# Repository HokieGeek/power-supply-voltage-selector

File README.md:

# power-supply-voltage-selector 
Trying to learn more electronics by building a circuit that lets me have different voltage outputs for use with other prototypes and mostly breadboards

## Prototype

# Schematics
## Primary

## Daughter

# Boards
## Primary

## Daughter

# Parts list
## ICs
* [ATTINY85](http://www.atmel.com/images/atmel-2586-avr-8-bit-microcontroller-attiny25-attiny45-attiny85_datasheet.pdf) - Drives the digi pot and shift register
* [LM7805CT](http://www.mouser.com/ds/2/149/LM7805-189995.pdf) - 5v voltage regulator for Vic
* [MIC2940](http://www.micrel.com/_PDF/mic2940.pdf) - Adjustable voltage regulator as target output regulator
* [MCP41010](http://ww1.microchip.com/downloads/en/DeviceDoc/11195c.pdf) - 10 kΩ digital potentiometer
* [SN74LS595N](http://www.ti.com/lit/ds/symlink/sn74ls596.pdf) - 8-bit shift registers with latches

## Discrete components
* 12V Transformer
* 4x 1N4007 Rectifiers
* 2x 47 µF Electrolytic capacitors
* 3x 0.1 µF Ceramic capacitors
* 1x 330 Ω Resistor network (SIL-6)
* 1x 10 kΩ 5% Resistors
* 2x 1 kΩ 5% Resistors
* 4x 3mm LEDs (green. To indicate selected voltage)
* 1x 3mm LED (red. To indicate that power is flowing from the wall)
* 1x USB-A Female
* LED Volt meter thingy (slightly redundant with the LEDs...)
* Toggle switch (turns on Vin)
* Momentatry switch (selects voltage)
* Jumpers and headers (Oh my!)

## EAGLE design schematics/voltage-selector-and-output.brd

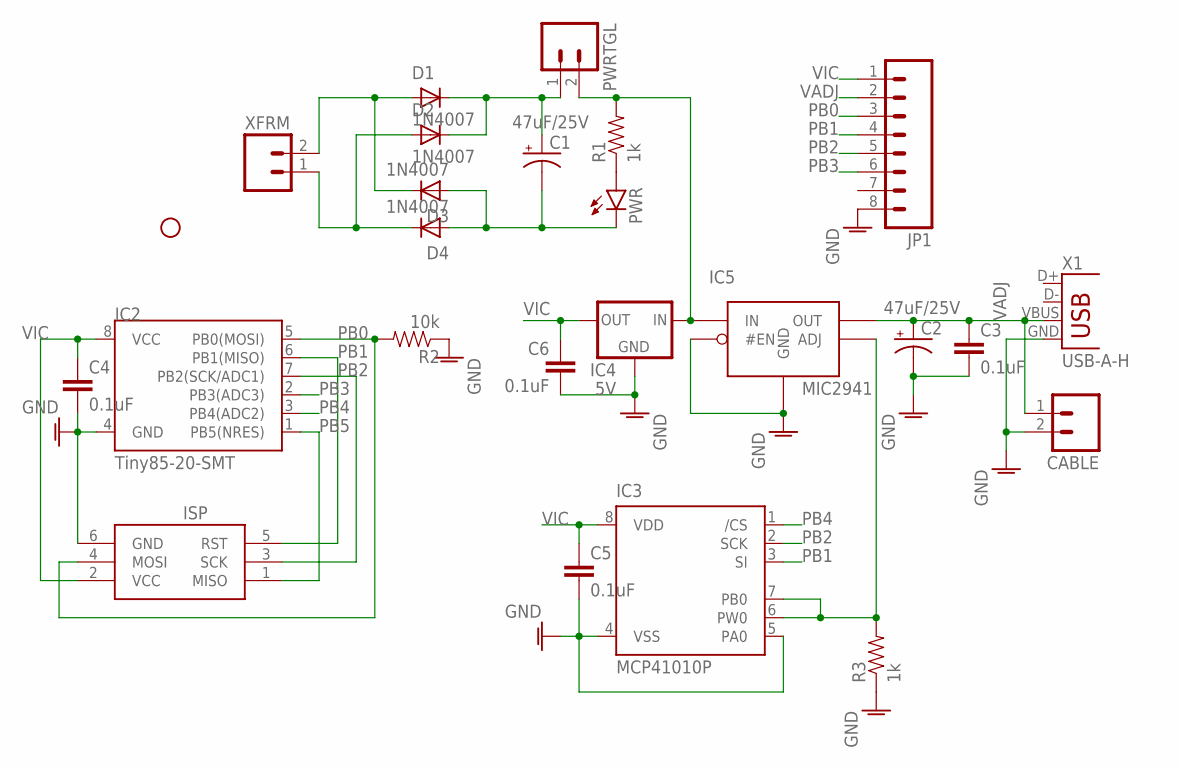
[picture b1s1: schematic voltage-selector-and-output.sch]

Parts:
C1, C2: 47uF/25V; E2,5-6
C3, C4, C5, C6: 0.1uF; 0805-CAP
CABLE: M02PTH; 1X02
D1, D2, D3, D4: 1N4007; SMA-DO214AC
IC2: Tiny85-20-SMT; SO08-EIAJ
IC3: MCP41010P; DIL8
IC4: 5V; 78XXS
IC5: MIC2941; TO220-5
ISP: AVRISP-6; AVRISP
JP1: M081X08; 1X08
PWR: LED-3MM-NO_SILK; LED3MM-NS
PWRTGL: M02PTH; 1X02
R1, R3: 1k; 0805
R2: 10k; 0805
STANDOFF1: STAND-OFF
X1: USB-A-H
XFRM: M02PTH; 1X02

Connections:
AGND: C2.-, C3.2, C4.2, C5.2, C6.2, CABLE.2, IC2.4 (GND), IC3.4 (VSS), IC3.5 (PA0), IC4.GND, IC5.2 (#EN), IC5.3 (GND), ISP.6 (GND), JP1.8, R2.1, R3.1, X1.GND
GND: D2.A, D4.K (C), XFRM.1
unnamed: IC3.6 (PW0), IC3.7 (PB0), IC5.1 (ADJ), R3.2
unnamed: D1.A, D3.K (C), XFRM.2
unnamed: PWR.A, R1.1
unnamed: C1.-, D3.A, D4.A, PWR.K (C)
unnamed: C1.+, D1.K (C), D2.K (C), PWRTGL.1
PB0: IC2.5 (PB0(MOSI)), ISP.4 (MOSI), JP1.3, R2.2
PB1: IC2.6 (PB1(MISO)), IC3.3 (SI), ISP.5 (RST), JP1.4
PB2: IC2.7 (PB2(SCK/ADC1)), IC3.2 (SCK), ISP.3 (SCK), JP1.5
PB3: IC2.2 (PB3(ADC3)), JP1.6
PB4: IC2.3 (PB4(ADC2)), IC3.1 (/CS)
PB5: IC2.1 (PB5(NRES)), ISP.1 (MISO)
VADJ: C2.+, C3.1, CABLE.1, IC5.5 (OUT), JP1.2, X1.VBUS
VCC: IC4.IN, IC5.4 (IN), PWRTGL.2, R1.2
VIC: C4.1, C5.1, C6.1, IC2.8 (VCC), IC3.8 (VDD), IC4.OUT, ISP.2 (VCC), JP1.1

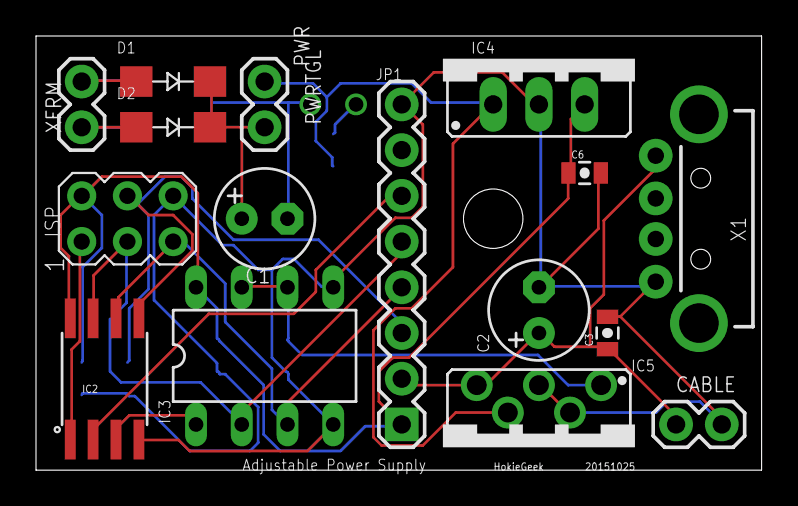
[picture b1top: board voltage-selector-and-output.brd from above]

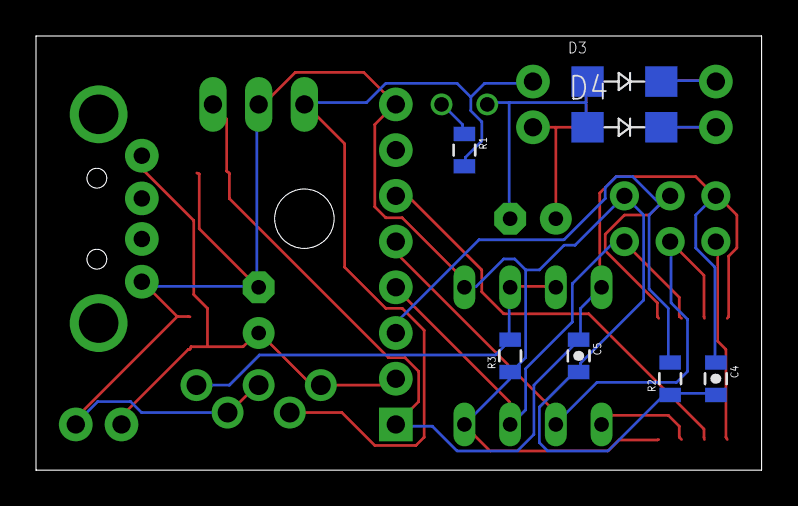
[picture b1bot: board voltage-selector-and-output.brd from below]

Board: 2 copper layers, 40.3 x 24.1 mm, 25 parts (7 on the bottom side), 16 nets.

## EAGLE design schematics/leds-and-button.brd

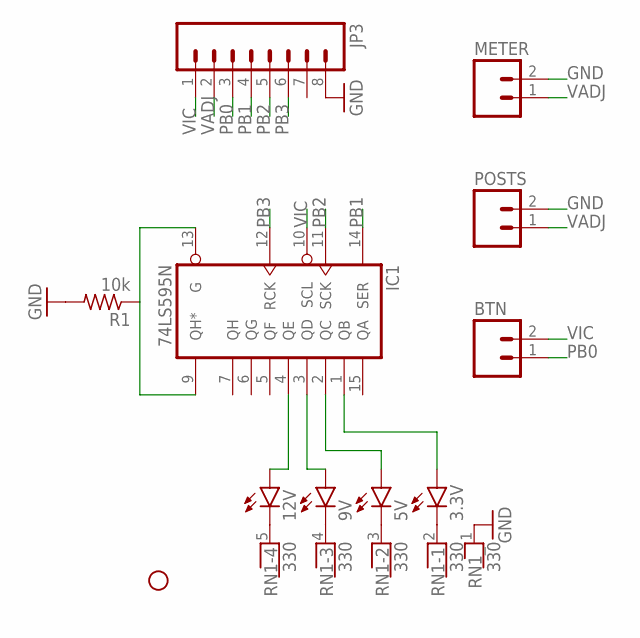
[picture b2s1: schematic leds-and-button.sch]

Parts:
3.3V, 5V, 9V, 12V: LED3MM
BTN: M02PTH; 1X02
IC1: 74LS595N; DIL16
JP2: STAND-OFF
JP3: M081X08; 1X08
METER: M02PTH; 1X02
POSTS: M02PTH; 1X02
R1: 10k; 0204V
RN1: 330; RN-6

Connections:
GND: IC1.8 (GND), JP3.8, METER.2, POSTS.2, R1.2, RN1.1
unnamed: 12V.K (C), RN1.5
unnamed: 9V.K (C), RN1.4
unnamed: 12V.A, IC1.4 (QE)
unnamed: 9V.A, IC1.3 (QD)
unnamed: 5V.A, IC1.2 (QC)
unnamed: 5V.K (C), RN1.3
unnamed: 3.3V.K (C), RN1.2
unnamed: IC1.9 (QH*), IC1.13 (G), R1.1
unnamed: 3.3V.A, IC1.1 (QB)
PB0: BTN.1, JP3.3
PB1: IC1.14 (SER), JP3.4
PB2: IC1.11 (SCK), JP3.5
PB3: IC1.12 (RCK), JP3.6
VADJ: IC1.16 (VCC), JP3.2, METER.1, POSTS.1
VIC: BTN.2, IC1.10 (SCL), JP3.1

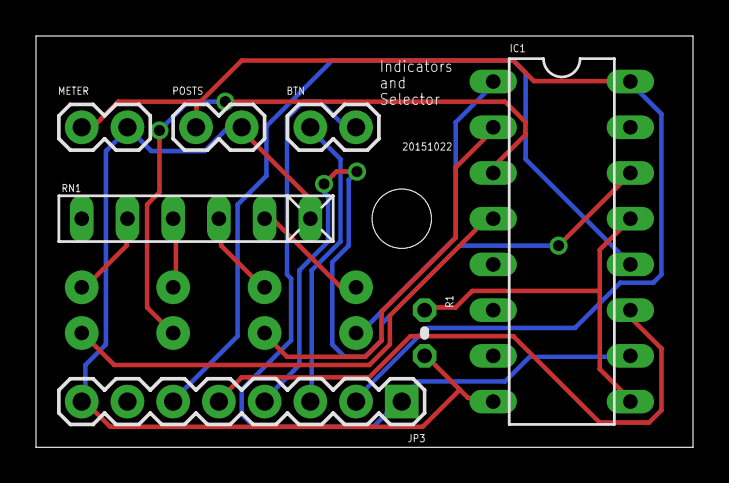
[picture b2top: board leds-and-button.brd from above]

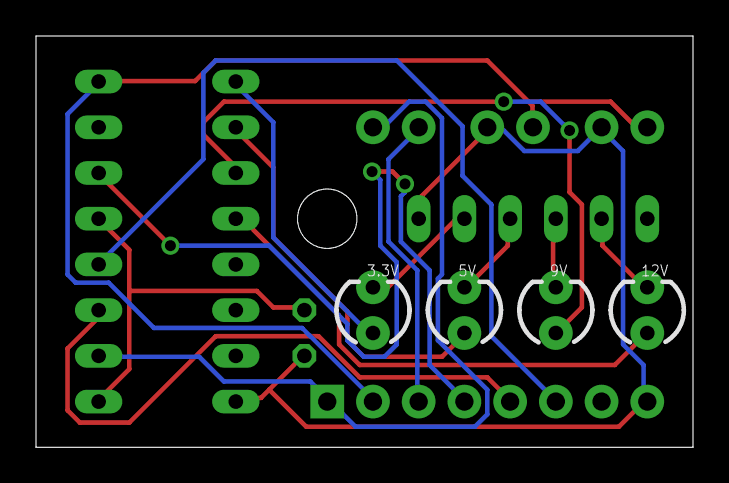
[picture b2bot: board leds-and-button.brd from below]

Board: 2 copper layers, 36.5 x 22.9 mm, 12 parts (4 on the bottom side), 16 nets.

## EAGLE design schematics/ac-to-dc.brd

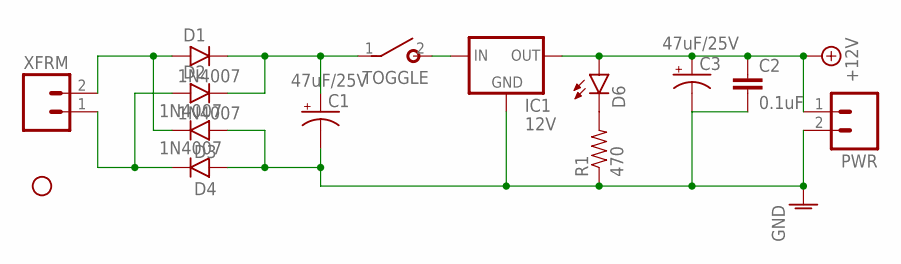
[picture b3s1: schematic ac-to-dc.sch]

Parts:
C1, C3: 47uF/25V; E2,5-6
C2: 0.1uF; CAP-PTH-SMALL
D1, D2, D3, D4: 1N4007; DO41-3
D6: LED-3MM-NO_SILK; LED3MM-NS
IC1: 12V; 78XXS
JP1: STAND-OFF
PWR: M02PTH; 1X02
R1: 470; AXIAL-0.4
TOGGLE: SPST
XFRM: M02PTH; 1X02

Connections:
+12V: C2.1, C3.+, D6.A, IC1.OUT, PWR.1
AGND: C1.-, C2.2, C3.-, D3.A, D4.A, IC1.GND, PWR.2, R1.P$1 (1)
unnamed: IC1.IN, TOGGLE.2 (S)
unnamed: D1.A, D3.C, XFRM.2
unnamed: D2.A, D4.C, XFRM.1
unnamed: D6.K (C), R1.P$2 (2)
unnamed: C1.+, D1.C, D2.C, TOGGLE.1

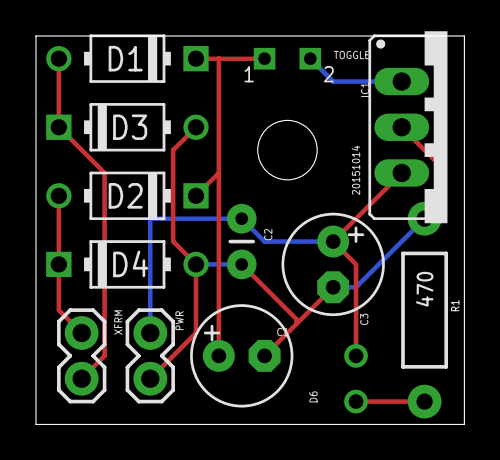
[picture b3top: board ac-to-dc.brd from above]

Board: 2 copper layers, 23.8 x 21.6 mm, 14 parts (0 on the bottom side), 7 nets.

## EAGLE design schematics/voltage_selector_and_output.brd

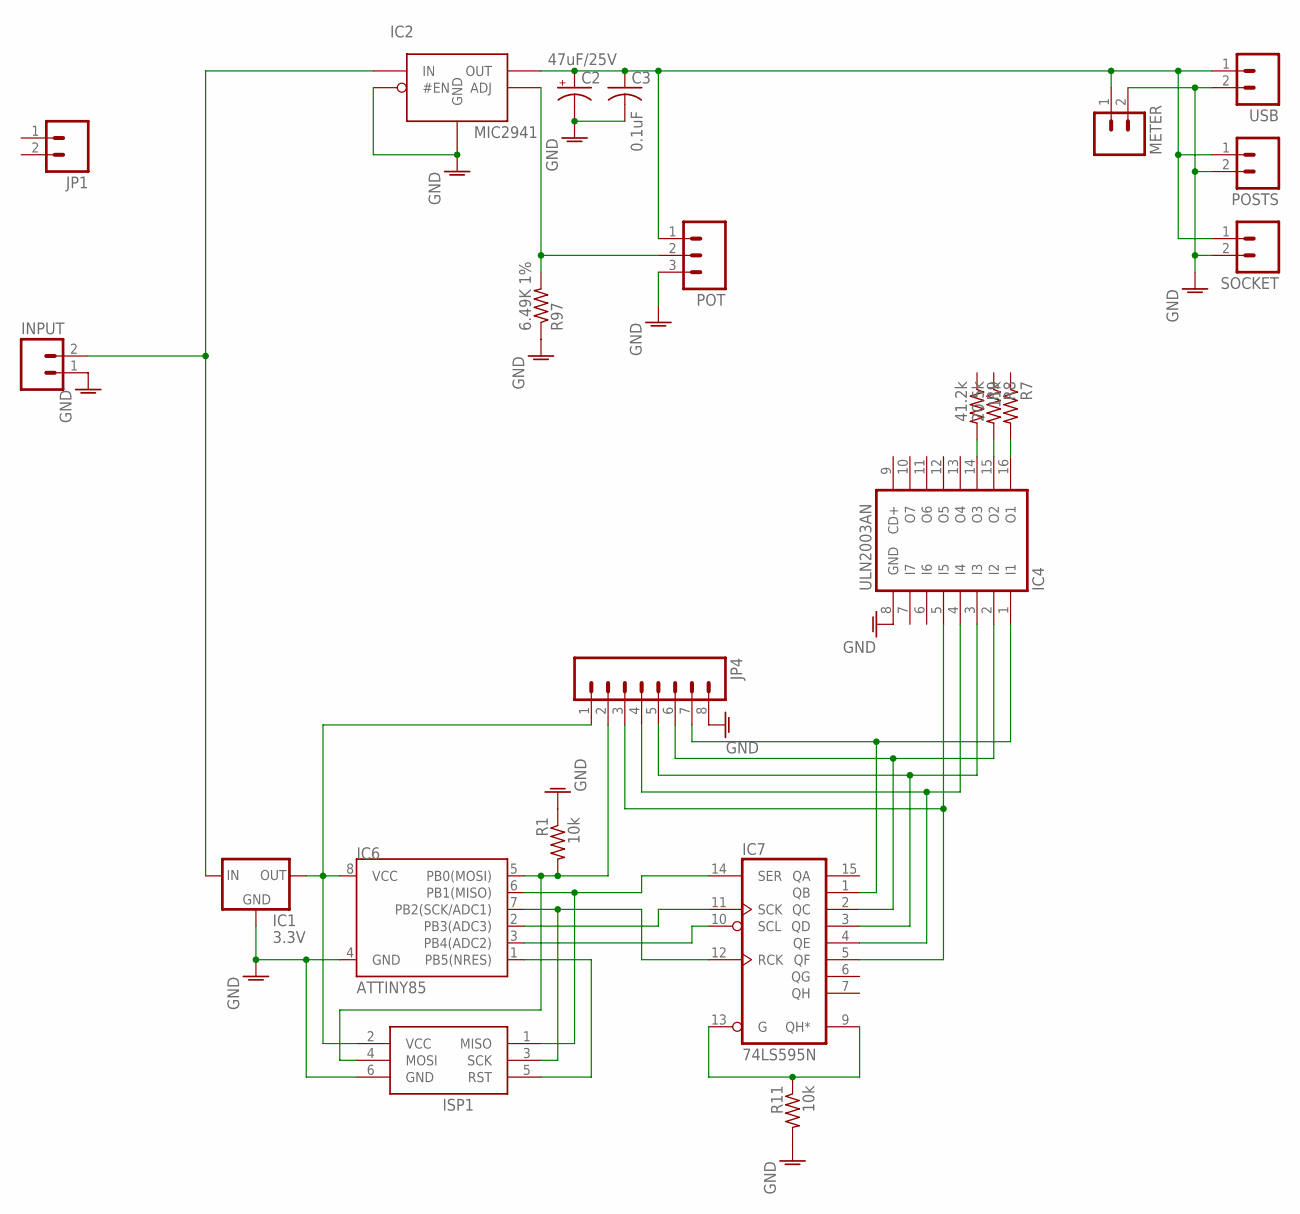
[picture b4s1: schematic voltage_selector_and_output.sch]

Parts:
C2: 47uF/25V; E2,5-6
C3: 0.1uF; C025-025X050
IC1: 3.3V; 78XXS
IC2: MIC2941; TO220-5
IC4: ULN2003AN; DIL16
IC6: ATTINY85; DIP08
IC7: 74LS595N; DIL16
INPUT: M02PTH; 1X02
ISP1: AVRISP-6; AVRISP
JP1: M02JST-PTH-2; JST-2-PTH
JP4: M081X08; 1X08
METER: M02PTH; 1X02
POSTS: M02PTH; 1X02
POT: M03PTH; 1X03
R1, R11: 10k; 0207/5V
R7: 11k; 0207/5V
R8: 20.5k; 0207/5V
R9: 41.2k; 0207/5V
R97: 6.49K 1%; 0207/5V
SOCKET: M02PTH; 1X02
USB: M02PTH; 1X02

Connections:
AGND: C2.-, C3.2, IC1.GND, IC2.2 (#EN), IC2.3 (GND), IC4.8 (GND), IC6.4 (GND), INPUT.1, ISP1.6 (GND), JP4.8, METER.2, POSTS.2, POT.3, R1.1, R11.2, R97.1, SOCKET.2, USB.2
GND: IC7.8 (GND)
ISP_VCC: IC1.OUT, IC6.8 (VCC), ISP1.2 (VCC), JP4.1
unnamed: IC1.IN, IC2.4 (IN), INPUT.2
unnamed: IC2.1 (ADJ), POT.2, R97.2
unnamed: IC6.1 (PB5(NRES)), ISP1.5 (RST)
unnamed: IC6.2 (PB3(ADC3)), IC7.11 (SCK)
unnamed: IC6.3 (PB4(ADC2)), IC7.10 (SCL)
unnamed: IC6.7 (PB2(SCK/ADC1)), IC7.12 (RCK), ISP1.3 (SCK)
unnamed: IC6.5 (PB0(MOSI)), ISP1.4 (MOSI), JP4.2, R1.2
unnamed: IC4.16 (O1), R7.2
unnamed: IC6.6 (PB1(MISO)), IC7.14 (SER), ISP1.1 (MISO)
unnamed: IC4.15 (O2), R8.2
unnamed: IC4.14 (O3), R9.2
unnamed: IC4.1 (I1), IC7.1 (QB), JP4.7
unnamed: IC4.2 (I2), IC7.2 (QC), JP4.6
unnamed: IC4.3 (I3), IC7.3 (QD), JP4.5
unnamed: IC4.4 (I4), IC7.4 (QE), JP4.4
unnamed: IC4.5 (I5), IC7.5 (QF), JP4.3
unnamed: IC7.9 (QH*), IC7.13 (G), R11.1
VADJ: C2.+, C3.1, IC2.5 (OUT), METER.1, POSTS.1, POT.1, SOCKET.1, USB.1
VCC: IC7.16 (VCC)

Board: 2 copper layers, 22 parts (0 on the bottom side), 20 nets, no tracks yet.

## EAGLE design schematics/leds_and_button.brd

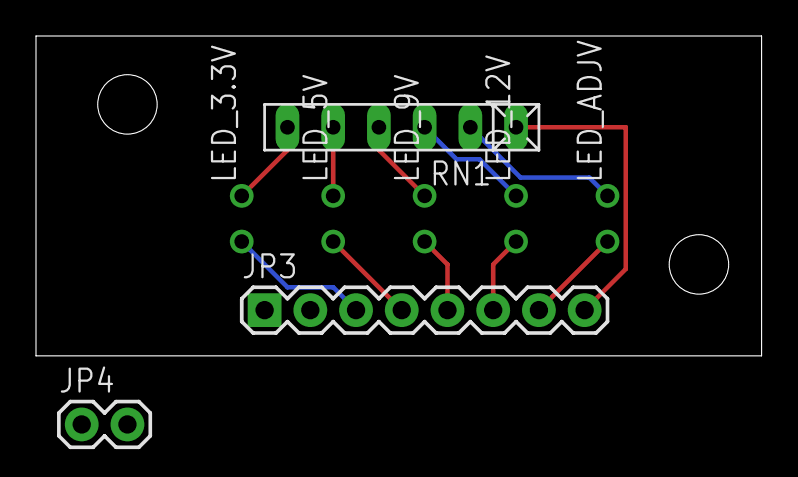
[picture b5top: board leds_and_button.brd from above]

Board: 2 copper layers, 40.3 x 17.8 mm, 10 parts (0 on the bottom side), 13 nets.

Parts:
JP1, JP2: STAND-OFF
JP3: 1X08
JP4: 1X02
LED_3.3V, LED_5V, LED_9V, LED_12V: LED3MM-NS
LED_ADJV: LED3MM-NS
RN1: 330; RN-6

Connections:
unnamed: JP3.8, RN1.1
unnamed: LED_3.3V.K, RN1.6
unnamed: LED_5V.K, RN1.5
unnamed: JP3.3, LED_3.3V.A
unnamed: JP3.4, LED_5V.A
unnamed: JP3.5, LED_9V.A
unnamed: JP3.6, LED_12V.A
unnamed: LED_9V.K, RN1.4
unnamed: LED_12V.K, RN1.3
unnamed: LED_ADJV.K, RN1.2
unnamed: JP3.1, JP4.2
unnamed: JP3.2, JP4.1
unnamed: JP3.7, LED_ADJV.A

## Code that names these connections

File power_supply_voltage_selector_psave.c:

#define F_CPU 8000000UL

#include <avr/io.h>
#include <avr/interrupt.h>
#include <avr/sleep.h>
#include <util/delay.h>

#include "eeprom.h"
#include "shiftregister.h"

//#define TIMER_PRESCALE ~(1<<WDP0)&~(1<<WDP1)&~(1<<WDP2)&~(1<<WDP3) // 16ms
#define TIMER_PRESCALE_MILLIS 16
//#define TIMER_PRESCALE (1<<WDP0) // 32ms
//#define TIMER_PRESCALE_MILLIS 32
//#define TIMER_PRESCALE (1<<WDP1) // 64ms
//#define TIMER_PRESCALE_MILLIS 64
//#define TIMER_PRESCALE (1<<WDP1) | (1<<WDP0) // 1/8s
//#define TIMER_PRESCALE_MILLIS 125
//#define TIMER_PRESCALE (1<<WDP2) // 1/4s
//#define TIMER_PRESCALE_MILLIS 250
//#define TIMER_PRESCALE (1<<WDP2) | (1<<WDP0) // 1/2s
//#define TIMER_PRESCALE_MILLIS 500
#define TIMER_TIMEOUT 2000 // 2s

#define BTN_DEBOUNCE_DELAY_MILLIS 25
#define BTN_DOUBLE_CLICK_DELAY_MILLIS 200
#define BUTTON_PIN PB0

#define SREG_PIN_DATA PB1
#define SREG_PIN_LATCHCLOCK PB2
#define SREG_PIN_SHIFTCLOCK PB3
#define SREG_PIN_RESET PB4

#define OPTIONS_RANGE_START 0b01000000
#define OPTIONS_RANGE_END 0b00000010

#define SELECTED_VOLTAGE_ADDRESS 0b01000000

typedef struct {
    int pinId;
    long lastReleaseTime;
    long lastDebounceTime;
    int state;
    int clickCount;
    void (*handler)(int, int, int);
} BUTTON_ITEM;

BUTTON_ITEM* handledButtons;
const ShiftRegister *const shiftReg;

uint8_t currentVoltage = OPTIONS_RANGE_START;

/* ================ TIME ================ */
long elapsedTime = 0;
uint8_t timerEnabled = 0;

long clock_diff(long old_clock, long new_clock) {
  if (new_clock >= old_clock)
    return new_clock - old_clock;
  else
    return new_clock + (65535 - old_clock);
}

/* ================ BUTTONS ================ */
BUTTON_ITEM* debouncedButton(int pin) {
    /*
    */

    BUTTON_ITEM* btn = &handledButtons[pin];

    if (timerEnabled == 0) {
        startTimer();
        btn->lastDebounceTime = 0;
        btn->lastReleaseTime = 0;
    }

    int currentState = (PINB & (1 << btn->pinId));

    cli();
    long time = elapsedTime;
    sei();

    if (currentState != btn->state) {
        btn->lastDebounceTime = time;
    } 

    if (!currentState) {
    // if (bit_is_clear(PINB, btn->pinId)) {
        btn->lastReleaseTime = time;
    }

    // if ((btn->lastDebounceTime > 0 && time > btn->lastDebounceTime) && ((time - btn->lastDebounceTime) >= BTN_DEBOUNCE_DELAY_MILLIS)) {
        btn->state = currentState;
        if ((btn->lastReleaseTime > 0 && time > btn->lastReleaseTime) && ((time - btn->lastReleaseTime) <= BTN_DOUBLE_CLICK_DELAY_MILLIS)) {
        // if ((time - btn->lastReleaseTime) <= BTN_DOUBLE_CLICK_DELAY_MILLIS) {
        // if (clock_diff(btn->lastReleaseTime, time) <= BTN_DOUBLE_CLICK_DELAY_MILLIS) {
            stopTimer();
            btn->clickCount = 2;
        } else {
            btn->clickCount = 1;
        }
    // }

    return btn;
}

void addButton(int pin, void (*handler)(int, int, int)) {
    // FIXME: need to check for range
    handledButtons[pin].pinId = pin;
    handledButtons[pin].lastDebounceTime = 0;
    handledButtons[pin].lastReleaseTime = 0;
    handledButtons[pin].state = 0;
    handledButtons[pin].handler = handler;
    handledButtons[pin].clickCount = 1;
}

void buttonsInit(int numPins) {
    int size = sizeof(BUTTON_ITEM)*numPins;
    handledButtons = (BUTTON_ITEM*)malloc(size);
    memset(handledButtons, 0, size);
}

void startTimer() {
    // Start the WDT
    if (timerEnabled == 0) {
        WDTCR |= (1<<WDIE); // Enable watchdog timer interrupts
        timerEnabled = 1;
    }
}

void stopTimer() {
    // Stop the WDT
    WDTCR &= ~(1<<WDIE); // Disable watchdog timer interrupts
    elapsedTime = 0L;
    timerEnabled = 0;
}

ISR(WDT_vect) {
    elapsedTime += TIMER_PRESCALE_MILLIS;
    if (elapsedTime >= TIMER_TIMEOUT)
        stopTimer();
}

ISR (PCINT0_vect) {
    // TODO: need to figure out which button was pressed
    //       PCINT****0**** denotes that PB0 was pressed
    BUTTON_ITEM* btn = debouncedButton(BUTTON_PIN);
    btn->handler(btn->pinId, btn->state, btn->clickCount);
}

void nextVoltage() {
    currentVoltage = currentVoltage >> 1;
    if (currentVoltage & OPTIONS_RANGE_END)
        currentVoltage = OPTIONS_RANGE_START;
    shiftBytes(currentVoltage);
}

void buttonHandler(int btnId, int state, int clickCount) {
    switch (btnId) {
    case BUTTON_PIN:
        if (state && clickCount == 2) {
            nextVoltage();
            EEPROM_write(SELECTED_VOLTAGE_ADDRESS, currentVoltage);
        }
       break;
    }
}

void init_pins() {
    shiftReg = InitShiftRegister(SREG_PIN_DATA, SREG_PIN_LATCHCLOCK,
                                 SREG_PIN_SHIFTCLOCK, SREG_PIN_RESET);

    // DDRB |= (1 << BUTTON_PIN); // pull-up resistor

    buttonsInit(1);
    addButton(BUTTON_PIN, &buttonHandler);
}

void init_interrupts() {
    PCMSK |= (1<<PCINT0); // Enable external interrupts PCINT0
    MCUCR  = (1<<ISC00);
    GIMSK |= (1<<PCIE); // Pin Change Interrupt Enable
 
    // WDTCR |= TIMER_PRESCALE;
    // WDTCR |= (1<<WDIE); // Enable watchdog timer interrupts

    sei(); // Enable global interrupts 
}

int main(void) {
    // 1. Read EEPROM for previous setting, set respective pins to high
    // 2. Go to sleep and wait for a button to be pushed
    // 3. Wake up when a button is pushed
    // 4. Determine which button (decode)
    // 5. If valid, write it to EEPROM
    // 6. Set respective pins
    // 7. Go back to bed

    uint8_t currVal = EEPROM_read(SELECTED_VOLTAGE_ADDRESS);
    // if (currVal & 0b11111111)
        // currVal = OPTIONS_RANGE_START;
    // TODO: some checks
    currentVoltage = currVal;

    init_pins();
    init_interrupts();

    ShiftBytes(shiftReg, currentVoltage);

    set_sleep_mode(SLEEP_MODE_PWR_DOWN); // Use the Power Down sleep mode

    for (;;) {
        sleep_mode();   // go to sleep and wait for interrupt...
    }
}

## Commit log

2013-11-15 Added the code I have so far
2013-11-15 Added Eagle schematics for this
2013-11-15 Found more schematics. Go figure
2014-03-29 Removed swap files that should have never been comitted
2015-10-09 Cleaning up the mess I left for myself
2015-10-09 Cleaning up the schematics directory
2015-10-13 Rethinking the transformer placement
2015-10-13 Added more pics
2015-10-14 Reworked the boards
2015-10-14 Ignore the stuffs
2015-10-14 Trying to make sense of my head 3 years ago! :)
2015-10-14 Added the datasheets to the readme because
2015-10-14 Added an LED to the ac-to-dc board
2015-10-15 Adding scripts that should really just be a single makefile
2015-10-15 Time to break up the band
2015-10-15 Fleshing out the eeprom bit
2015-10-15 Fleshing out the shift register stuff
2015-10-15 Sort of like a Makefile
2015-10-15 Always with the project file changing
2015-10-15 This seems to sort of work
2015-10-15 Cleaned up the makefile so it's less of a mess
2015-10-15 Don't know how I forgot this
2015-10-15 *sigh*
2015-10-15 Just writing the idea down.
2015-10-16 Removing extra copy
2015-10-16 Creating buttons.h
2015-10-16 Making use of split up files
2015-10-16 Pulled code out of the main source file
2015-10-16 Removing possibly redundant scripts
2015-10-16 Went for it
2015-10-16 Got it to compile!
2015-10-16 It is ridiculously late for me. Good night
2015-10-16 Uploaded it and it worked. Huzzah!
2015-10-16 Changed the pins because of reasons
2015-10-16 Adding code for using the AVR SPI interface
2015-10-16 Keeping it simple, I think
2015-10-17 Got SPI comm to the digi pot working!
2015-10-17 Moved the spi initializer to where it belongs
2015-10-18 Finally updated the primary schematic
2015-10-18 Removing files unused in this branch
2015-10-18 Changed how I determine the voltage selected
2015-10-18 Trying to set the pot as well as the register
2015-10-18 Changed the pin being used for the pot SI
2015-10-19 Updated the readme because
2015-10-19 Doing the LEDs first now and seeing if that works out (it does not)
2015-10-19 Resized board boundary to what I have room for and removed transistor array
2015-10-19 Finally got to working on the main board layout
2015-10-19 Moved the shift register to the top board since I have more room there and on the bottom board and I get to free up some pins on the jumper
2015-10-19 Doing this instead of working out. Yup
2015-10-19 Added pic of current progress
2015-10-20 Trying to deconflict the digi pot and register pins
2015-10-20 Want to use it as I want to use it
2015-10-20 The proj changed
2015-10-20 LED was all wrong, of course
2015-10-20 Removed resetting the register on init and only enables a reset pin if provided
2015-10-20 Put some actual thought at pin deconflicting
    and I think I got it right this time.
2015-10-20 Changing method name for spi
2015-10-20 Renabling the USI code I had
2015-10-20 Adding pins for USI
2015-10-20 Adding the USI SPI command
2015-10-20 Fixing an incorrect comment that was misleading
2015-10-21 Trying to figure out what I was doing
2015-10-21 The pot and shift register are finally working harmonously! w00t!
2015-10-21 Updated the schematics
2015-10-21 Removed need for shift register as we do not need it
2015-10-21 While I technically got it working, it is doing the LEDs in reverse order and does nothing with the pot
2015-10-21 I thought maybe using USI for the pot would make it work. It did not but I am leaving it in
2015-10-21 Fixing byte order issue in shift register software write
2015-10-21 Changed the bit order of the shift register data
2015-10-21 Expanding things a bit to make it more generic
2015-10-21 Definitely don't need a reset
2015-10-22 Reverted the shift stuff because I guess it works...?
2015-10-22 Trying to figure out why USI for SPI does not work
2015-10-22 Well, it's getting close but it's horribly slow... go figure...
2015-10-22 More infos
2015-10-22 Gotta make use of the preview option X-D
2015-10-23 Played around with the board for the leds
2015-10-24 Decided to remove the "adjustable" option because it was kinda useless
2015-10-24 Updated the prototype pic
2015-10-25 Optimizing the location of the components on the board and fixing the schematic
2015-10-25 The 12v regulator was kinda too much, now that I think about it
2015-10-26 Tweak tweak
2015-10-26 Figured out the error in my drawing, finally
2015-10-26 Silly...
2015-10-26 Tweaks
2015-10-26 Decided to give SMT another chance
2015-10-26 Added capacitor for the 5v reg
2015-10-26 Smaller and smaller. Gotta save on them bucks!
2015-10-27 This version's autorouter is way better than the older
2015-11-17 I do not need this here
2015-11-20 Updating to use container-based Travis infrastructure
2015-11-20 Adding a target to get the size of the binary
2015-11-20 Adding size check
2015-11-20 Whoops
2015-11-22 Tiny tweaks
2015-11-23 Changing the size command to be smarter

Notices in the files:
parts and their libraries:
SparkFun: Licensing: CC v3.0 Share-Alike You are welcome to use this library for commercial purposes.
SparkFun-LED: Licensing: Creative Commons ShareAlike 4.0 International - https://creativecommons.org/licenses/by-sa/4.0
